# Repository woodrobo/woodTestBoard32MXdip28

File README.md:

# woodTestBoard32MXdip28

PIC32MX2xxのDIP28ピンマイコンの評価ボードです。「お手軽DIPマイコンのPIC32MXを始めよう(仮称)」に対応しています。

BOOTH(https://woodrobo.booth.pm/items/3751749)で販売しています。

## USBピンヘッダについて  
USBコネクタの近くに2つピンヘッダがついていると思います。これはUSB関連の接続をするためものです。単純な回路ですので詳細は回路図をご覧ください。  
  
USB B SELECT  
USB Bコネクタ(パソコンと接続する時のコネクタ)のUSB通信線(D+,D-)の配線をすることができます。B-CH340で接続すればUSBシリアル変換ICを利用することができます。(ArduinoでいうSerial.printでパソコンに文字を表示できるようになる)B-PICで接続すれば下にあるPIC MCU USB TESTのDEVICE(B)に配線をつなげることができます。  
  
PIC MCU USB TEST  
PICマイコンのUSB関連の配線をすることができます。PIC-DEVICE(B)で接続＆USB B SELECTでB-PICで接続すればPICをUSB Bコネクタに繋げられUSB DEVICE機能を試すことができます。PIC-HOST(A)で接続すればUSB Aコネクタに繋げられUSB HOST機能を試すことができます。  
VBUS-5VはUSBモジュール使用の時に必要になることがあるので繋げておいてください。	  
  
# 書き込みについて  
ボード右側にあるICSP用ピンヘッダは 写真のように三角マークがあるピンがMCLRです。書き込み器には同じように三角マークがあるので三角マーク同士を合わせるように接続してください。例えばPickit3では写真のように書き込み器の裏面が見えるような向きになると思います。  

# 部品について

(はんだづけする際に見る)部品表や(部品を購入する際に見る)部品個数表はadd_infoフォルダを見てください。  
価格は1部品あたりの値段を計算していますので複数個入りで販売されている部品に関しては購入金額はこれよりも高くなります。  
チップ部品セットとがBoothで販売しているチップコンデンサ、抵抗、LEDがセットになったものです。

# はんだづけ

向きを間違えやすい箇所を説明します。

U1のCH340は上下2つある白線のうち伸びている箇所(左上)がピン1です。そのため写真のような向きではんだづけしてください。

D1のチップLEDは写真のような向きです。チップLEDの裏面のほうが分かりやすいため裏面にしたLEDも横に並べています。

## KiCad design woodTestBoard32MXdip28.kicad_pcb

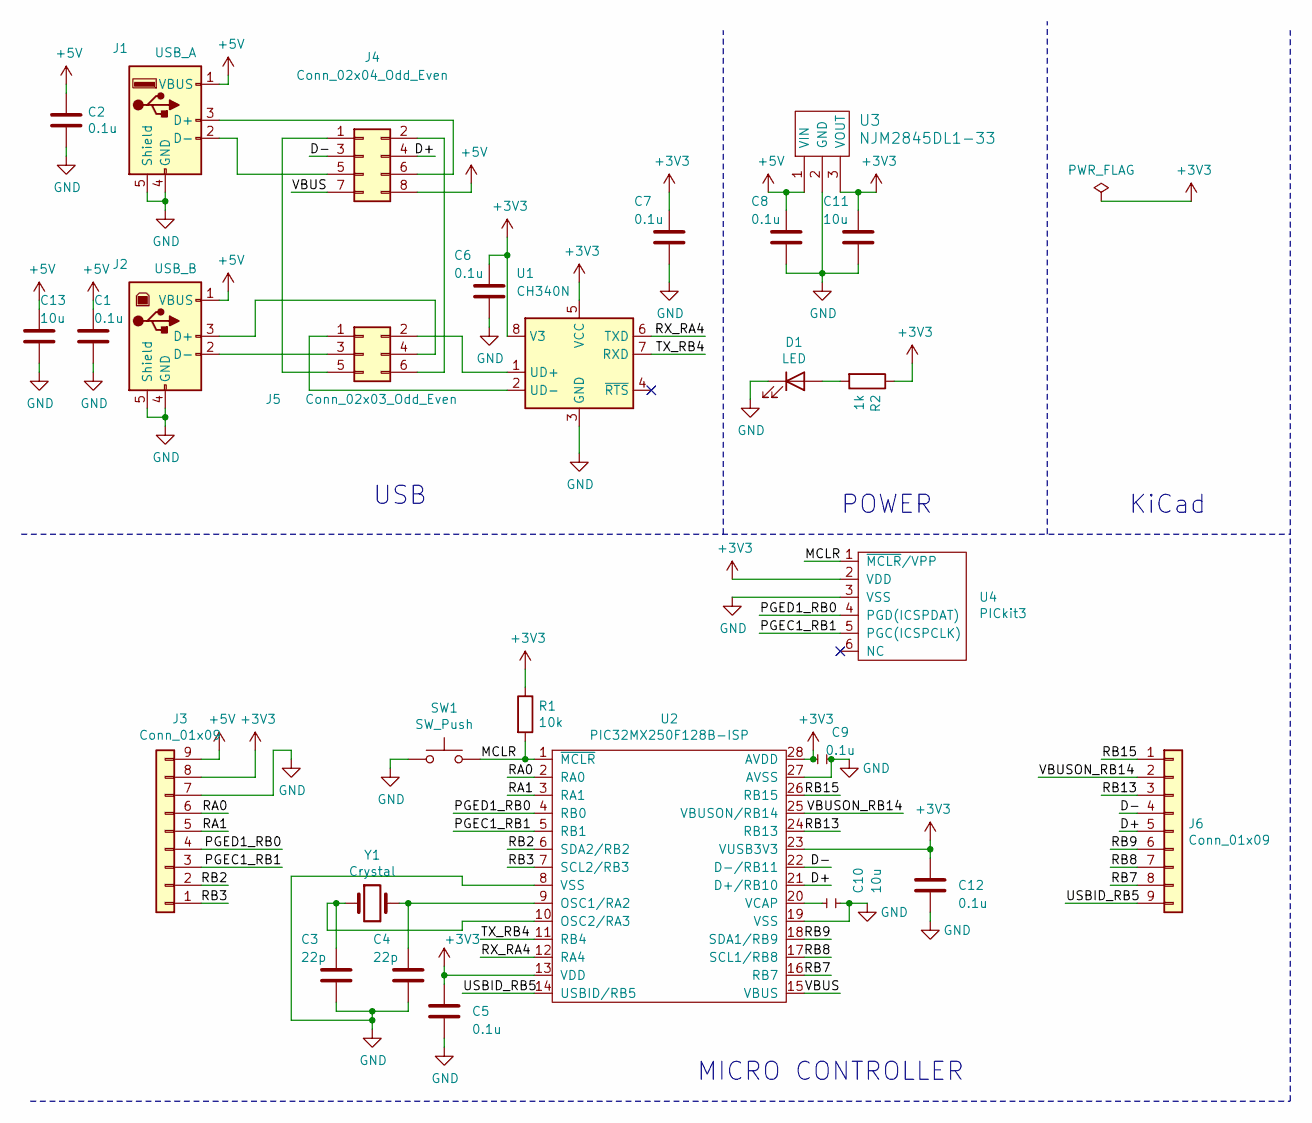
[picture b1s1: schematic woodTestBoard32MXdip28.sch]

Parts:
C1, C2, C5, C6, C7, C8, C9, C12: 0.1u; C_0603_1608Metric_Pad1.05x0.95mm_HandSolder
C3, C4: 22p; C_0603_1608Metric_Pad1.05x0.95mm_HandSolder
C10, C11, C13: 10u; C_0603_1608Metric_Pad1.05x0.95mm_HandSolder
D1: LED; LED_0603_1608Metric_Pad1.05x0.95mm_HandSolder
J1: USB_A; USB_A_Stewart_SS-52100-001_Horizontal
J2: USB_B; USB_B_OST_USB-B1HSxx_Horizontal
J3, J6: Conn_01x09; PinSocket_1x09_P2.54mm_Vertical
J4: Conn_02x04_Odd_Even; PinHeader_2x04_P2.54mm_Vertical
J5: Conn_02x03_Odd_Even; PinHeader_2x03_P2.54mm_Vertical
R1: 10k; R_0603_1608Metric_Pad1.05x0.95mm_HandSolder
R2: 1k; R_0603_1608Metric_Pad1.05x0.95mm_HandSolder
SW1: SW_Push; SW_TVAF06-A020B-R
U1: CH340N; SOIC-8_3.9x4.9mm_P1.27mm
U2: PIC32MX250F128B-ISP; DIP-28_W7.62mm_Socket
U3: NJM2845DL1-33; TO-252-2
U4: PICkit3; PinHeader_1x06_P2.54mm_Horizontal
Y1: Crystal; Crystal_HC49-U_Vertical

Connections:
+3V3: C5.1, C6.1, C7.1, C9.1, C11.1, C12.1, J3.8, R1.1, R2.1, U1.5 (VCC), U1.8 (V3), U2.13 (VDD), U2.23 (VUSB3V3), U2.28 (AVDD), U3.3 (VOUT), U4.2 (VDD)
+5V: C1.1, C2.1, C8.1, C13.1, J1.1 (VBUS), J2.1 (VBUS), J3.9, J4.8, U3.1 (VIN)
/D+: J4.4, J6.5, U2.21 (D+/RB10)
/D-: J4.3, J6.4, U2.22 (D-/RB11)
/MCLR: R1.2, SW1.2, U2.1 (~MCLR), U4.1 (~MCLR~/VPP)
/PGEC1_RB1: J3.3, U2.5 (RB1), U4.5 (PGC(ICSPCLK))
/PGED1_RB0: J3.4, U2.4 (RB0), U4.4 (PGD(ICSPDAT))
/RA0: J3.6, U2.2 (RA0)
/RA1: J3.5, U2.3 (RA1)
/RB2: J3.2, U2.6 (SDA2/RB2)
/RB3: J3.1, U2.7 (SCL2/RB3)
/RB7: J6.8, U2.16 (RB7)
/RB8: J6.7, U2.17 (SCL1/RB8)
/RB9: J6.6, U2.18 (SDA1/RB9)
/RB13: J6.3, U2.24 (RB13)
/RB15: J6.1, U2.26 (RB15)
/RX_RA4: U1.6 (TXD), U2.12 (RA4)
/TX_RB4: U1.7 (RXD), U2.11 (RB4)
/USBID_RB5: J6.9, U2.14 (USBID/RB5)
/VBUS: J4.7, U2.15 (VBUS)
/VBUSON_RB14: J6.2, U2.25 (VBUSON/RB14)
GND: C1.2, C2.2, C3.2, C4.2, C5.2, C6.2, C7.2, C8.2, C9.2, C10.1, C11.2, C12.2, C13.2, D1.1 (K), J1.4 (GND), J1.5 (Shield), J2.4 (GND), J2.5 (Shield), J3.7, SW1.1, U1.3 (GND), U2.8 (VSS), U2.19 (VSS), U2.27 (AVSS), U3.2 (GND), U4.3 (VSS)
unnamed: C3.1, U2.10 (OSC2/RA3), Y1.1
unnamed: C4.1, U2.9 (OSC1/RA2), Y1.2
unnamed: C10.2, U2.20 (VCAP)
unnamed: D1.2 (A), R2.2
unnamed: J1.2 (D-), J4.5
unnamed: J1.3 (D+), J4.6
unnamed: J2.2 (D-), J5.3
unnamed: J2.3 (D+), J5.4
unnamed: J4.1, J5.5
unnamed: J4.2, J5.6
unnamed: J5.1, U1.2 (UD-)
unnamed: J5.2, U1.1 (UD+)

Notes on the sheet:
USB
POWER
MICRO CONTROLLER
KiCad

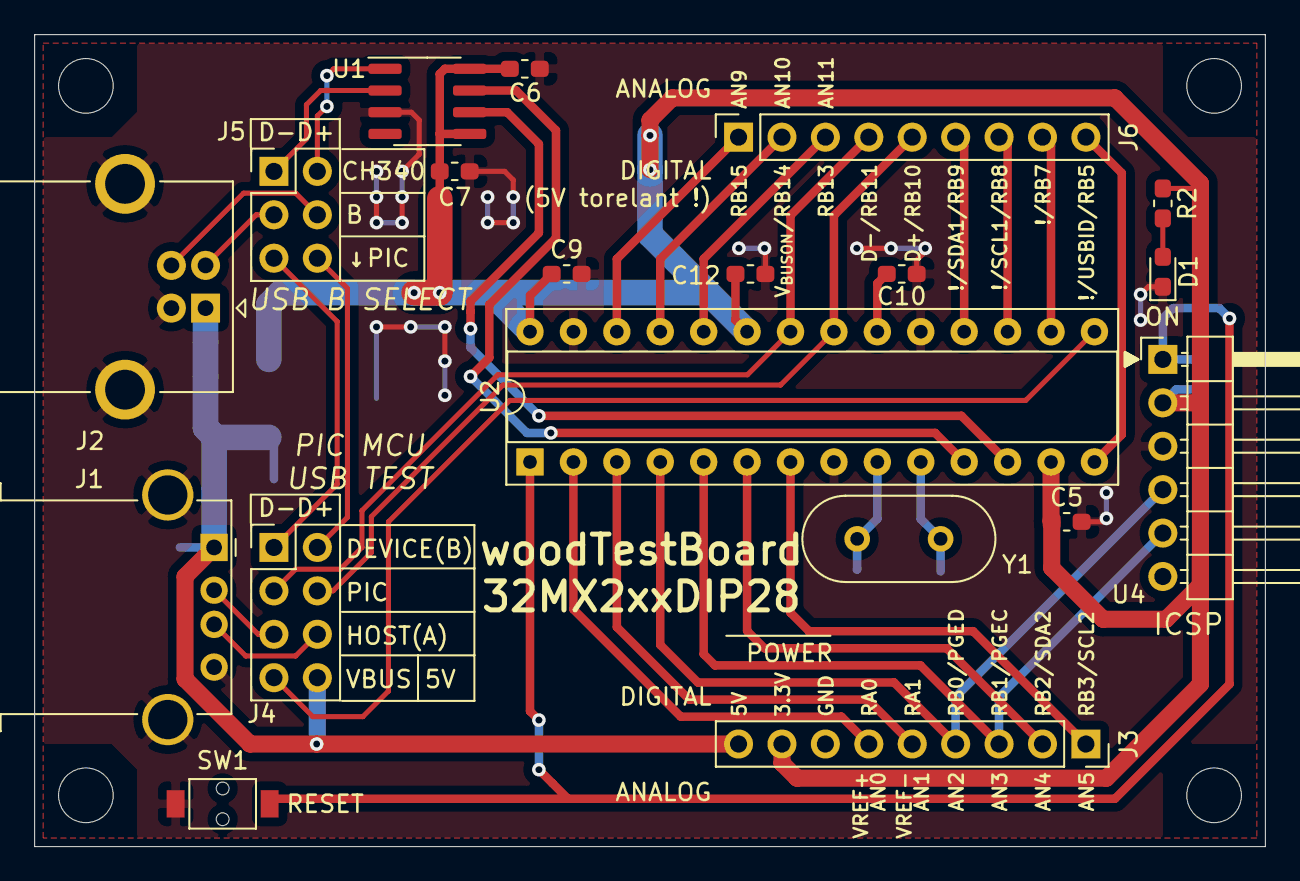
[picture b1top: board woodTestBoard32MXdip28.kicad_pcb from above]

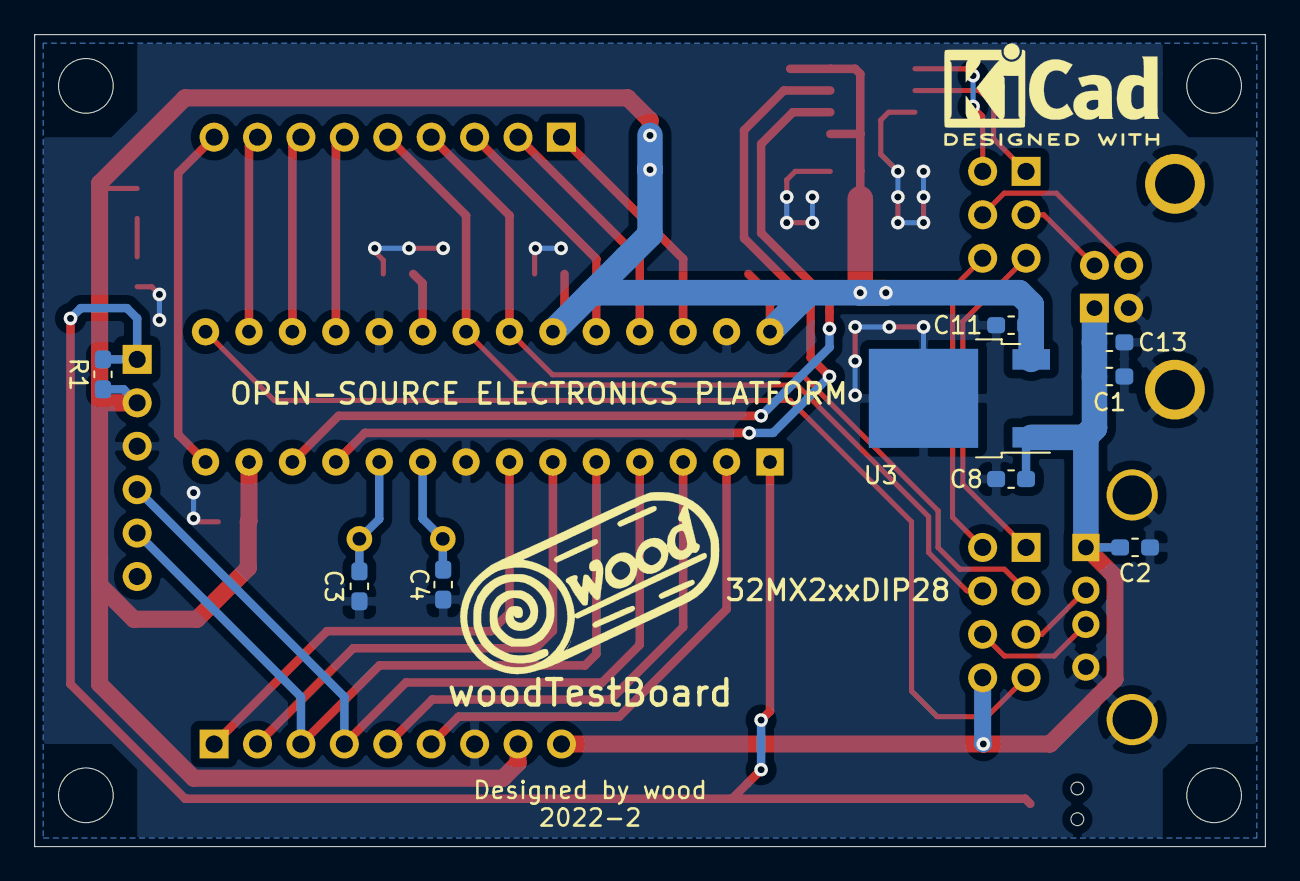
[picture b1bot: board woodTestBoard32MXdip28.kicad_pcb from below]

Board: 2 copper layers, 72.0 x 47.5 mm, 32 parts (9 on the bottom side), 34 nets.

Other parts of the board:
 : MountingHole_3.2mm_M3
 #2,  #3,  #4: MountingHole_3.2mm_M3

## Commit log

2022-03-24 完成した回路
2022-03-24 説明追加
2022-03-24 説明修正
2022-03-26 BOOTH対応
2022-04-03 USBピンヘッダの説明を追加
2022-04-18 ICSP接続の説明を追加
